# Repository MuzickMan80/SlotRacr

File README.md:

Materials:
1 x HDMI Cable ($6) [https://www.adafruit.com/product/2775]
1 x Raspberry Pi 3 A+ ($25) [https://www.adafruit.com/product/4027]
1 x 5v 2.5a supply ($8) [https://www.adafruit.com/product/1995]
1 x 8GB SD Card
8 x Photo Transistor ($4) [https://www.adafruit.com/product/2831]
8 x 5.6kohm Resistor ($1)
8 x 1kohm Resistor ($1)

F to M jumper wires ($2) [https://www.adafruit.com/product/1954]
1 x Breadboard ($5) [https://www.adafruit.com/product/64]

1 x HDMI Display ($42) [https://www.amazon.com/Yasoca-Inch-Monitor-HDMI-Raspberry/dp/B089YSHMYS/ref=sr_1_19?dchild=1&keywords=hdmi%2Bdisplay%2B7%2Binch&qid=1612496742&refinements=p_85%3A2470955011&rnid=2470954011&rps=1&sr=8-19&th=1]
Total: $93

Raspberry Pi setup:
1. Using Belena Etcher, burn Raspbian Lite OS image to the SD Card
1. Connect keyboard and monitor to Raspberry Pi, and let it startup
1. Login using username 'pi' and password 'raspberry'
1. Run 'sudo raspi-config' to enable WiFi and login to your network
  1. Select System Options->Wireless LAN and enter your SSID and password
  1. Select Interface Options->SSH to enable SSH access to your Raspberry Pi
1. Restart the Raspberry Pi to let it connect to your network
1. Run 
1. After it reboots, login again, and type the 'ifconfig' command to get the IP address for your network

From your computer:
1. Copy files to Raspbery Pi `./deploy.sh <pi ip>`

## References
https://disconnected.systems/blog/custom-rpi-image-with-github-travis/#travis
https://medium.com/platformer-blog/creating-a-custom-raspbian-os-image-for-production-3fcb43ff3630

## Ideas
Stop oog timer when red
Min 3 laps notice of low gas
Save race results
Online results database
Local sounds when low on gas

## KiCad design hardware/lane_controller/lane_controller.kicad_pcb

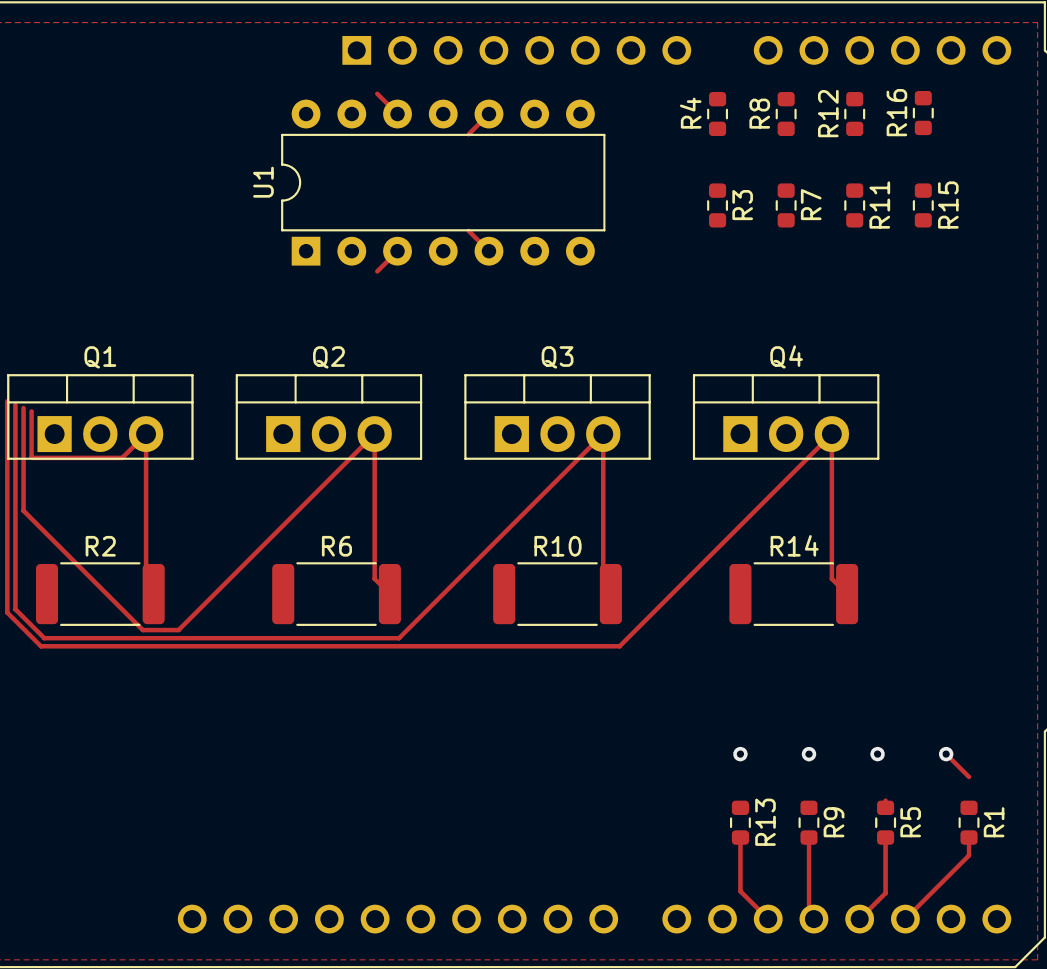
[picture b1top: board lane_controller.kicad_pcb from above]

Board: 2 copper layers, 22 parts (0 on the bottom side), 22 nets.

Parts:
A1: Arduino_UNO_R3
Q1, Q2, Q3, Q4: IRLZ34N; TO-220-3_Vertical
R1, R5, R9, R13: 100; R_0603_1608Metric
R2, R6, R10, R14: 0R01; R_2512_6332Metric
R3, R7, R11, R15: 1.2K; R_0603_1608Metric
R4, R8, R12, R16: 10K; R_0603_1608Metric
U1: MCP6004; DIP-14_W7.62mm

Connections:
+3V3: A1.4, U1.4
/A0: A1.9, R4.2, U1.1
/A1: A1.10, R8.2, U1.7
/A2: A1.11, R12.2, U1.8
/A3: A1.12, R16.2, U1.14
/PWM0: A1.17, R1.2
/PWM1: A1.18, R5.2
/PWM2: A1.19, R9.2
/PWM3: A1.20, R13.2
GND: A1.6, A1.7, A1.29, R2.1, R3.2, R6.1, R7.2, R10.1, R11.2, R14.1, R15.2, U1.11
unnamed: Q1.1, R1.1
unnamed: Q1.3, R2.2, U1.3
unnamed: Q2.1, R5.1
unnamed: Q2.3, R6.2, U1.5
unnamed: Q3.1, R9.1
unnamed: Q3.3, R10.2, U1.10
unnamed: Q4.1, R13.1
unnamed: Q4.3, R14.2, U1.12
unnamed: R3.1, R4.1, U1.2
unnamed: R7.1, R8.1, U1.6
unnamed: R11.1, R12.1, U1.9
unnamed: R15.1, R16.1, U1.13

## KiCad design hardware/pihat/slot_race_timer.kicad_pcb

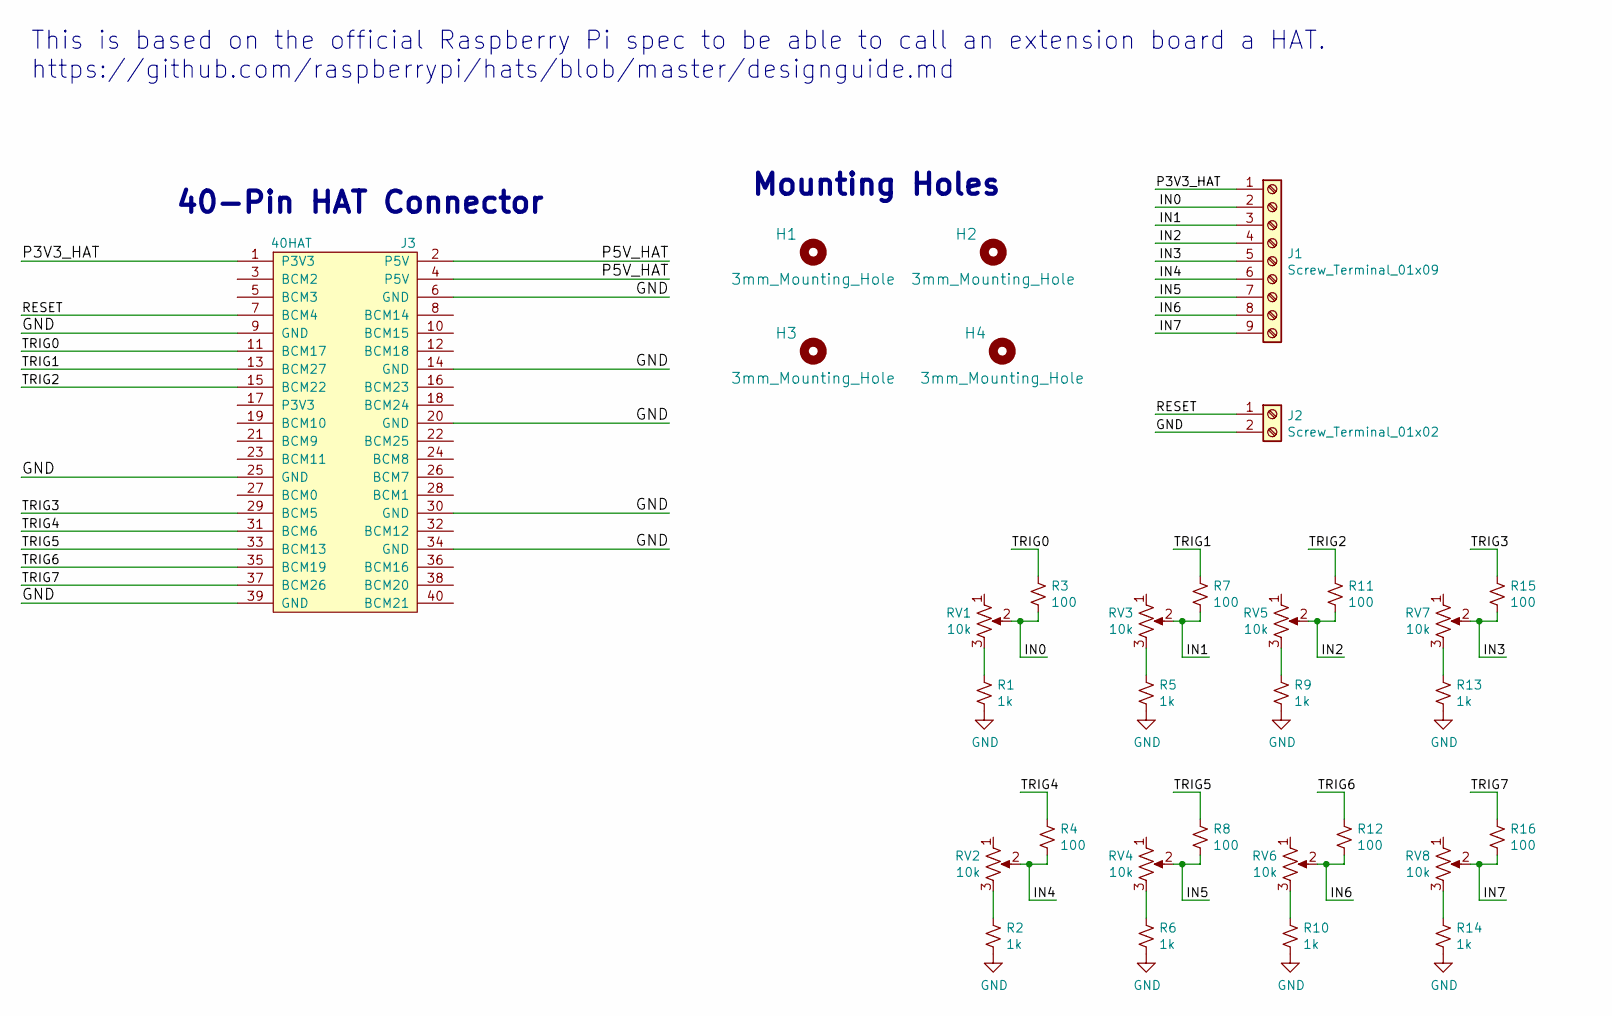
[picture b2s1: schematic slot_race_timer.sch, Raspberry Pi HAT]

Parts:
H1, H2, H3, H4: 3mm_Mounting_Hole; NPTH_3mm_ID
J1: Screw_Terminal_01x09; PhoenixContact_MSTBA_2,5_9-G-5,08_1x09_P5.08mm_Horizontal
J2: Screw_Terminal_01x02; PhoenixContact_MSTBA_2,5_2-G-5,08_1x02_P5.08mm_Horizontal
J3: 40HAT; PinSocket_2x20_P2.54mm_Vertical
R1, R2, R5, R6, R9, R10, R13, R14: 1k; R_Axial_DIN0204_L3.6mm_D1.6mm_P2.54mm_Vertical
R3, R4, R7, R8, R11, R12, R15, R16: 100; R_Axial_DIN0204_L3.6mm_D1.6mm_P2.54mm_Vertical
RV1, RV2, RV3, RV4, RV5, RV6, RV7, RV8: 10k; Potentiometer_Bourns_3339P_Vertical

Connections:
/IN0: J1.2, R3.2, RV1.2
/IN1: J1.3, R7.2, RV3.2
/IN2: J1.4, R11.2, RV5.2
/IN3: J1.5, R15.2, RV7.2
/IN4: J1.6, R4.2, RV2.2
/IN5: J1.7, R8.2, RV4.2
/IN6: J1.8, R12.2, RV6.2
/IN7: J1.9, R16.2, RV8.2
/P3V3_HAT: J1.1, J3.1 (P3V3)
/RESET: J2.1, J3.7 (BCM4)
/TRIG0: J3.11 (BCM17), R3.1
/TRIG1: J3.13 (BCM27), R7.1
/TRIG2: J3.15 (BCM22), R11.1
/TRIG3: J3.29 (BCM5), R15.1
/TRIG4: J3.31 (BCM6), R4.1
/TRIG5: J3.33 (BCM13), R8.1
/TRIG6: J3.35 (BCM19), R12.1
/TRIG7: J3.37 (BCM26), R16.1
GND: J2.2, J3.6 (GND), J3.9 (GND), J3.14 (GND), J3.20 (GND), J3.25 (GND), J3.30 (GND), J3.34 (GND), J3.39 (GND), R1.2, R2.2, R5.2, R6.2, R9.2, R10.2, R13.2, R14.2
unnamed: R1.1, RV1.3
unnamed: R2.1, RV2.3
unnamed: R5.1, RV3.3
unnamed: R6.1, RV4.3
unnamed: R9.1, RV5.3
unnamed: R10.1, RV6.3
unnamed: R13.1, RV7.3
unnamed: R14.1, RV8.3

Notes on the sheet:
Mounting Holes
40-Pin HAT Connector
This is based on the official Raspberry Pi spec to be able to call an extension board a HAT. https://github.com/raspberrypi/hats/blob/master/designguide.md

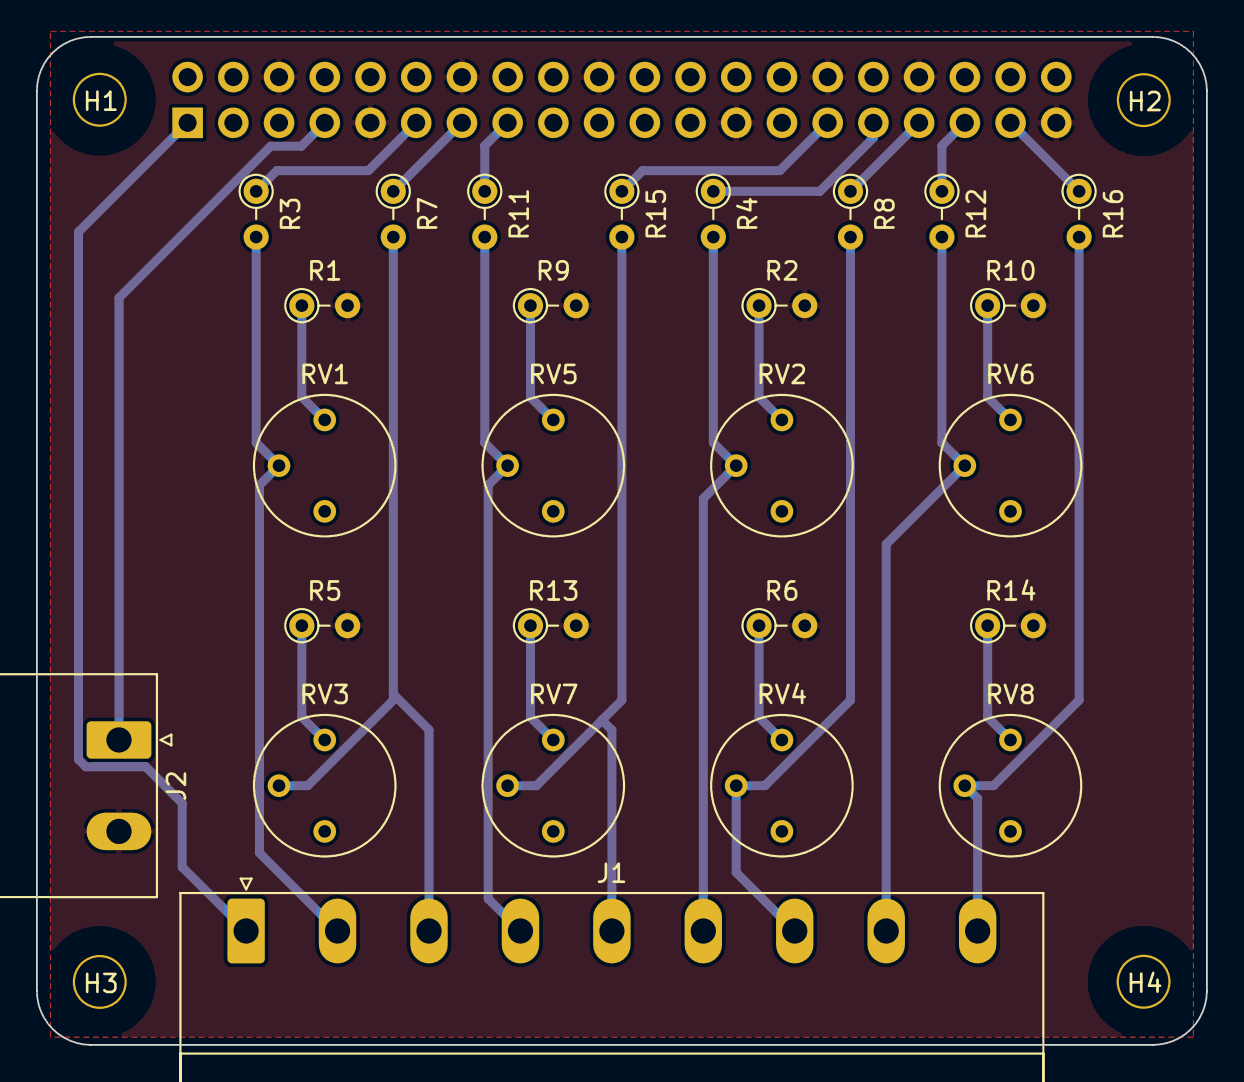
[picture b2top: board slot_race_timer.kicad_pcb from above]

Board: 2 copper layers, 65.0 x 56.0 mm, 31 parts (1 on the bottom side), 27 nets.

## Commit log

2021-02-07 Initial checkin
2021-02-07 Create install scripts
2021-02-07 Add Python Frontend, remove angular frontend
2021-02-07 remove angular frontend gitignore
2021-02-07 Ignore pycache
2021-02-08 Refactory python frontend
2021-02-09 Some finishing touches
2021-06-13 Refactor backend, add UTs
2021-06-13 Restore Web Frontend
2021-06-13 Add deploy scripts
2021-06-14 Cleanup backend service
2021-06-14 Add nav bar
2021-06-14 remove mat-sidenav-menu
2021-06-16 Add navigation
2021-12-12 Update pinout
2021-12-12 Starting to add settings
2021-12-12 Update paths
2021-12-12 Remove BackEnd folder
2021-12-12 Commit auto-update scripts
2021-12-12 Fix post_update path
2021-12-12 Set executable flag
2021-12-12 Set +x on app.py
2021-12-12 Run timer_update after network online
2021-12-12 Fix invocation of post_update from update service
2021-12-12 App IP address to main page
2021-12-12 Pass event loop into io manager
2021-12-12 Remove service installation from post_update
2021-12-12 Add timer_update to wants
2021-12-12 Launch UI after network online
2021-12-12 Enable pullup on reset button
2021-12-12 Refresh entire cell rectangle when dirty
2021-12-27 Reorganize backend
2021-12-27 Add name to backend
2021-12-27 Test animated backgrounds
2021-12-27 Fix checkerboard rendering
2021-12-27 Add openjpeg requirement
2021-12-27 Fix apt-get missing sudo
2021-12-27 Show driver info
2021-12-27 Show SDL driver name
2021-12-28 Reorganize frontend
2021-12-28 Restore 2.0 pygame version
2021-12-28 Fix compatibility with 3.7
2021-12-28 Improve status layout
2021-12-28 Downgrade to pygame 1.9.6
2021-12-28 Get sdl ttf
2021-12-28 Improve exception handling
2021-12-28 Disable cursor
2021-12-28 install disable_cursor
2021-12-28 Add kivy test app
2021-12-28 improve deploy script
2021-12-28 Improve teardown, prepare for lane state
2021-12-28 Refactor track manager
2021-12-29 Adding settings to the backend
2021-12-29 First pass settings api
2021-12-29 Move pin assignments into io managers
2021-12-29 Finish what I started
2021-12-29 Add pit logic to backend
2021-12-29 Add states to frontend
2021-12-29 temporarily disable reset button
2021-12-29 Fix pit error
2021-12-29 Fix build
2021-12-29 Debug pitting
2021-12-29 Fix pit pin
2021-12-29 Fix lane serialization
2021-12-30 Update pit logic
2021-12-30 cleanup pit reset
2021-12-30 Implement penalty
2021-12-30 Fix pitting
2021-12-30 Fix pitting probabilities
2021-12-30 Update service files on change
2021-12-30 Fix syntax error
2021-12-30 remove temporary ip in backend
2021-12-30 remove temporary ip in backend code
2021-12-30 Change to 10 laps to out of fuel
2021-12-30 Change status names
2021-12-30 Change to lane 4
2022-01-08 Add cors to backend
2022-01-09 Add lane name settings
2022-01-09 Add settings persistance
2022-01-09 Ignore settings.json file
2022-01-09 Add web frontend
2022-01-09 Start of logging module
2022-01-09 Commit lane controller board
2022-01-09 Remove duplicate assets, disable nginx
2022-01-10 Fix root web access
2022-01-10 Attempt to fix settings saving
2022-01-10 Update favicon
2022-01-10 Fix persistence, improve settings layout
2022-01-16 implement support for lane controller
2022-01-16 Fix some bugs
2022-01-16 lane controller test
2022-01-16 Adjust lane speed
2022-01-16 test
2022-01-16 switch to 5
2022-01-16 throttle when in penalty
2022-01-16 fix freq
2022-01-30 change lane mapping to match hardware
2022-01-30 send commands at startup
2022-01-31 commit hardware
2022-01-31 Add lane name setting
2022-02-03 Fix settings rest API
2022-02-12 Commit arduino source
2022-02-12 Fixup settings
2022-02-12 Start to add logging
2022-02-12 Ignore read errors
2022-02-12 Ignore blank lines in return ?!?
2022-02-12 Improvements to lane controller
2022-02-12 Change working directory to home
2022-02-12 Fix web frontend after moving working directory
2022-02-12 Add setting for out of fuel laps
2022-02-12 And add to settings list
2022-02-13 Fix pit number of laps setting
2022-02-13 Fix startup issue if lane_controller can't be connected
2022-02-13 Catch error when starting
2022-02-13 Hook up require crew alert setting
2022-02-13 Add track simulator setting
2022-02-13 Fix simulator ?
2022-02-13 Remove throttle column from frontend
2022-02-13 Fix startup issue with lane table
2022-02-13 Ensure settings are restored and saved as correct type
2022-02-14 Cleanup and test pit code
2022-02-14 Cleanup lane indexing issues
2022-02-14 Refactor lane_controller to be owned by io_manager
2022-02-15 Flags and cleanup
2022-02-16 Fix frontend
2022-02-19 Refactor and cleanup
2022-02-19 Fix lane sorting
2022-02-19 Refactor lane settings
2022-02-19 Add support for disabling the simulator
2022-02-19 Improve out of fuel algorithm
2022-02-19 Fix pit progress
2022-02-19 Update frontend while pitting
2022-02-19 Fix pit progress formatting
2022-02-19 Improve timing accuracy
2022-02-19 Parameterize pit timing
2022-02-19 Fix second fuel stop
2022-02-19 Add setting for changing lane's slow speed
2022-02-19 Adjust oof settings, expose settings to frontend
2022-02-19 Expose max crew alert time
2022-02-19 Allow pitting under yellow
2022-02-19 Use current tick on pit button
2022-02-19 Pit button debugging
2022-02-19 More debugging
2022-02-19 fix get_current_tick
2022-02-19 Prevent penalty when car already slow
2022-02-19 Fix typo
2022-02-19 Pit debugging
2022-02-19 Don't reset under_yellow on pitting
2022-02-19 Fix pit times
2022-02-19 Auto pit after penalty
2022-02-19 Remove debug logging
2022-09-05 Checkin hardware files
2022-09-05 Cleanup tests, improve code coverage
2022-09-05 Add light controller
2022-09-05 Rearrange USB ports
2022-09-07 Force pit when out of gas
2022-09-07 Add text font for driver and status
2022-09-11 expose io
2022-09-11 Swap hardcoded lane controller
2022-09-11 Restore light loopback mode
2022-09-11 Add light loopback, software control
2022-09-12 Add accident support
2022-09-19 Rate limit update messages
2022-09-19 Add set_accident method to pit
2022-09-20 Update backend
2022-09-20 Update web frontend to include race manager
2022-09-20 Add pit info to frontend
2022-09-20 Allow cancelling accident pit while in pits
2022-09-21 Update pit_info.py
    tapping -> taping
2022-09-21 Update lane_table.py
    Always update pit info
2022-09-23 Fix a few things (hopefully)
2022-09-23 Fix state buttons
2022-09-23 Update pit_info only once
2022-09-23 Ramp up lane power
2022-09-23 Change min lap time to 3.5
2022-09-23 Fix reset
2022-09-24 Update pit_info.py
    Add additional pit infos
2023-01-28 Update layout to give more room for pit info
2023-01-28 Add slowdown per accident
2023-01-28 Add crew names to pit messages
2023-01-28 Fix ShaggySlimSlick bug
2023-01-28 Add penalty message
2023-01-28 Improve penalty messaging
2023-02-18 Keep oog duty always
2023-02-18 Initialize logger
2023-02-18 update logger config loading
2023-02-18 call init_logger on construction
2023-02-18 add lane power logger
2023-02-18 fix lane logger
2023-02-18 disable socketio logger
2023-02-18 Stop immediately, fix burst on track power change
2023-10-17 Add station registration
2023-10-21 Add registration support
2023-10-21 Add pit time to lane state
2023-10-21 Update web interface
2023-10-21 Fix message transmission
2023-10-21 Unregister other badges, notify observers
2023-10-21 Fix /registration url conflict
2023-10-21 Initial station script
2023-10-21 Fix update script to be username agnostic
2023-10-21 Install vim, fix post_boot.sh
2023-10-21 Cleanup initial install of pigpiod
2023-10-21 Add dhcp server to eth0
2023-10-21 Fix post_boot
2023-10-22 add update_stations shell script
2023-10-22 Update attached stations
2023-10-22 Install python requirements on station
2023-10-22 Fix update_stations.sh script
2023-10-22 Get pyusb installed on stations
2023-10-22 Switch to ogg files, parse station update
2023-11-04 Add race sounds
2023-11-04 Add station service
2023-11-04 enable git-lfs
2023-11-04 force gitlfs fetch after update
2023-11-04 Enable executable permissions on station.py
2023-11-04 Update path to trackid
2023-11-04 Stop running station before updating it
2023-11-04 Process lange updates to play sounds
2023-11-04 pygame requirements are causing issues on stations
2023-11-04 Run station service as root
2023-11-04 Fix missing 'usb'
2023-11-04 +x station.py
2023-11-04 Fix flags and pos
2023-11-04 Kill station service
2023-11-04 Reboot stations after update
2023-11-04 Only play background sounds when real race is running
2023-11-04 Play green sound when enough people start
2023-11-04 Delay one track by 1 second
2023-11-04 Add track reset to web frontend
2023-11-04 Move button
2024-02-20 Improve reliability of card scanner
2024-02-26 Add evdev to requirements
2024-02-26 Update station update script
2024-02-26 Fix update stations script
2024-02-26 Add pip upgrade
2024-02-29 Fix tests
2024-02-29 Don't run out of gas under red
2024-03-05 Wait up to 30 seconds for git pull to succeed
